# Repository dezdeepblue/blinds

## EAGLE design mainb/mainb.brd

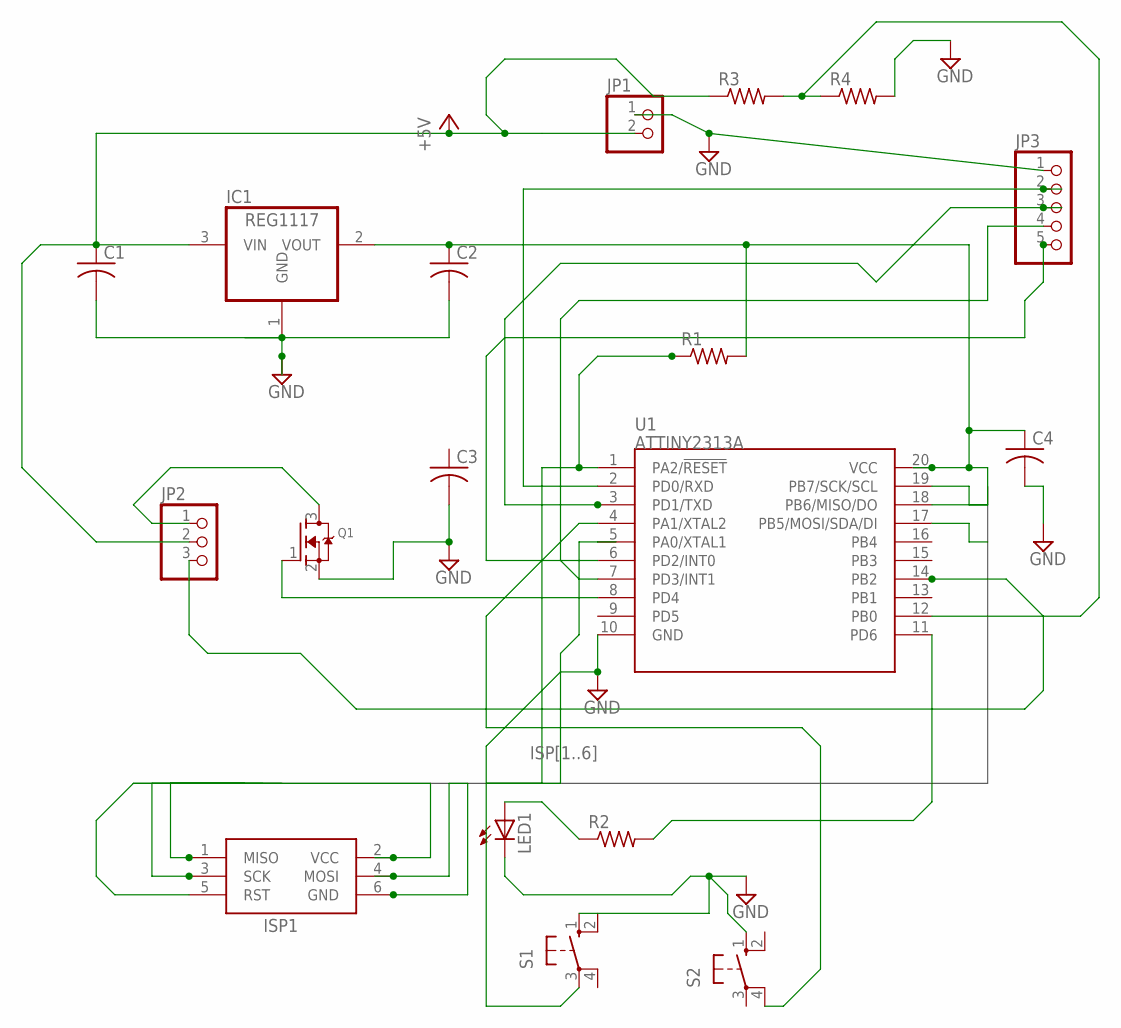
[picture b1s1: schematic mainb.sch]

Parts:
C1, C2, C3, C4: C-USC0603; C0603
IC1: REG1117; SOT223
ISP1: AVRISP-6; AVRISP
JP1: PINHD-1X2; 1X02
JP2: PINHD-1X3; 1X03
JP3: PINHD-1X5; 1X05
LED1: LEDSML0603; SML0603
Q1: MOSFET-NREFLOW; SOT23
R1, R2, R3, R4: R-US_R0603; R0603
S1, S2: 10-XX; B3F-10XX
U1: ATTINY2313A; SOP20W

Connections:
+5V: C1.1, IC1.3 (VIN), JP1.2, JP2.2, R3.1
GND: C1.2, C2.2, C3.2, C4.2, IC1.1 (GND), JP1.1, JP3.1, LED1.C, Q1.2 (S), R4.2, S1.1 (S), S2.1 (S)
ISP1: ISP1.1 (MISO), U1.18 (PB6/MISO/DO)
ISP2: C2.1, C4.1, IC1.2 (VOUT), ISP1.2 (VCC), R1.2, U1.20 (VCC)
ISP3: ISP1.3 (SCK), U1.19 (PB7/SCK/SCL)
ISP4: ISP1.4 (MOSI), U1.17 (PB5/MOSI/SDA/DI)
ISP5: ISP1.5 (RST), R1.1, U1.1 (PA2/!RESET)
ISP6: ISP1.6 (GND), U1.10 (GND)
unnamed: JP2.1, Q1.3 (D)
unnamed: JP3.3, U1.3 (PD1/TXD)
unnamed: JP3.2, U1.2 (PD0/RXD)
unnamed: JP3.4, U1.7 (PD3/INT1)
unnamed: JP3.5, U1.6 (PD2/INT0)
unnamed: JP2.3, U1.14 (PB2)
unnamed: Q1.1 (G), U1.8 (PD4)
unnamed: R3.2, R4.1, U1.12 (PB0)
unnamed: R2.2, U1.11 (PD6)
unnamed: LED1.A, R2.1
unnamed: S1.3, U1.5 (PA0/XTAL1)
unnamed: S2.4 (P1), U1.4 (PA1/XTAL2)

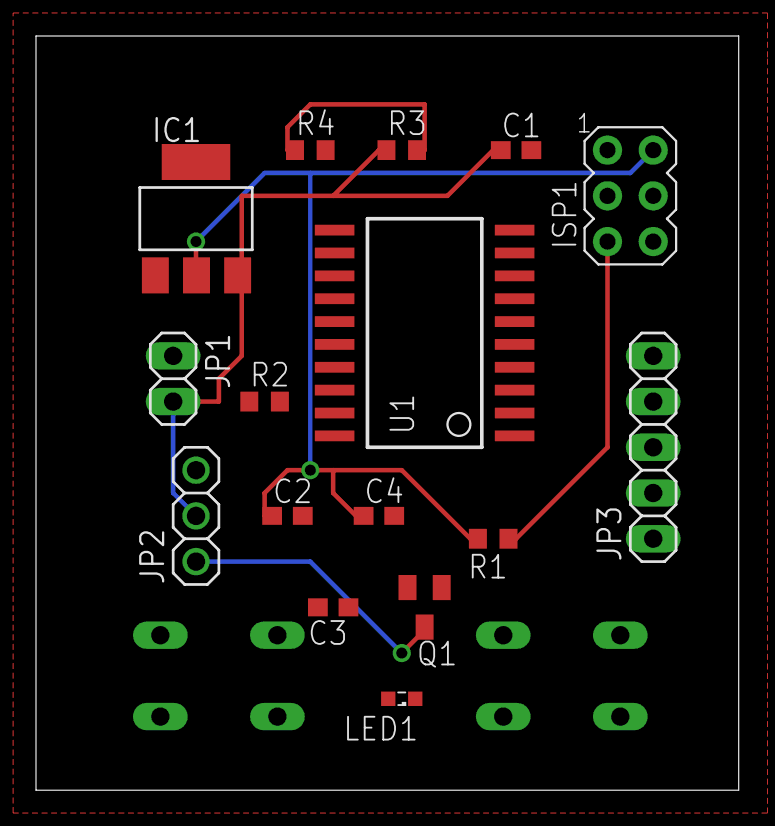
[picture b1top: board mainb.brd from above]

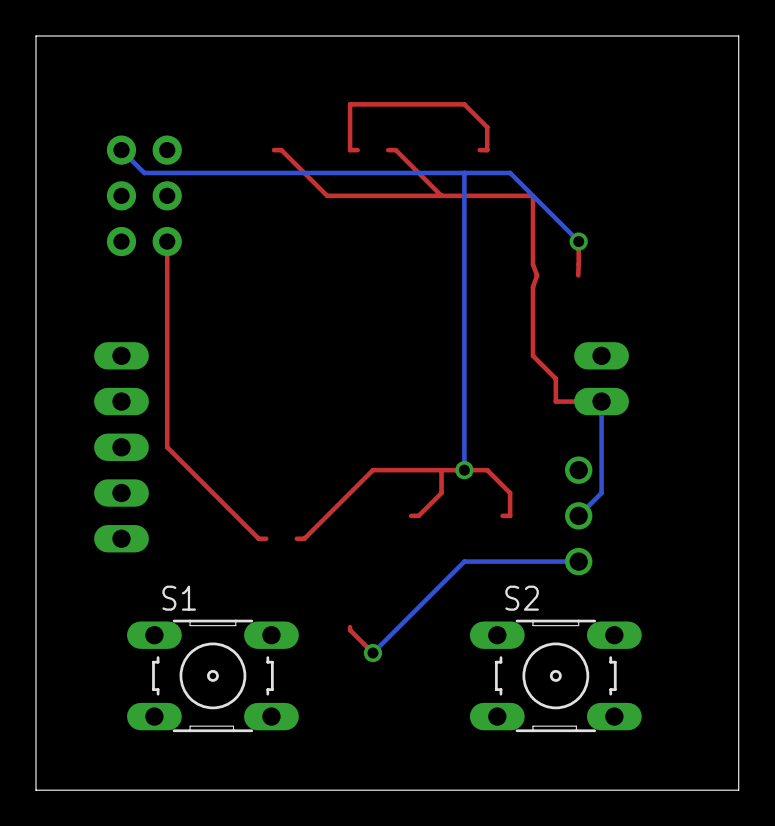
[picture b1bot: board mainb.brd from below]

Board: 2 copper layers, 39.0 x 41.9 mm, 18 parts (2 on the bottom side), 20 nets.

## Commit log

2014-07-02 added bunch
2014-07-03 started some coding
2014-07-09 scad files done
2014-07-09 added in both pcs
2014-07-09 added filament compensation to frame-base and wall-server components
2014-07-09 added more compenstaion variables
2014-07-10 scad changest to almost all files ready for reprint
2014-07-13 changed wall width to 42 - changed style to plugin for fan adapter changed width of frame base to 26 changed adapters - now there are fan adapters on both side
2014-07-13 minor changes to rounded corners
2014-07-14 cad files edit'ed again for sizing/change slot1 fitting.
2014-07-15 changed to references file
2014-07-15 added inventor ref file and created front wall in inventor
2014-07-16 some inventor junk
2014-07-17 all autodesk walls done and cover
2014-07-18 added servo part
2014-07-19 added a file for sunil
2014-07-21 minor changes
2014-07-21 breakout inventor files
2014-07-21 Created inventor dir and stls
2014-07-22 inventor stls - make arm fit within walls
2014-07-25 added channel to the arm-slot and end-wall for adapters
2014-07-26 added kicad files
2014-07-27 kicad file done
2014-07-29 added sunil stuff and playing around with eagle etc

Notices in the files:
parts and their libraries:
SparkFun-DigitalIC: Licensing: Creative Commons ShareAlike 4.0 International - https://creativecommons.org/licenses/by-sa/4.0
